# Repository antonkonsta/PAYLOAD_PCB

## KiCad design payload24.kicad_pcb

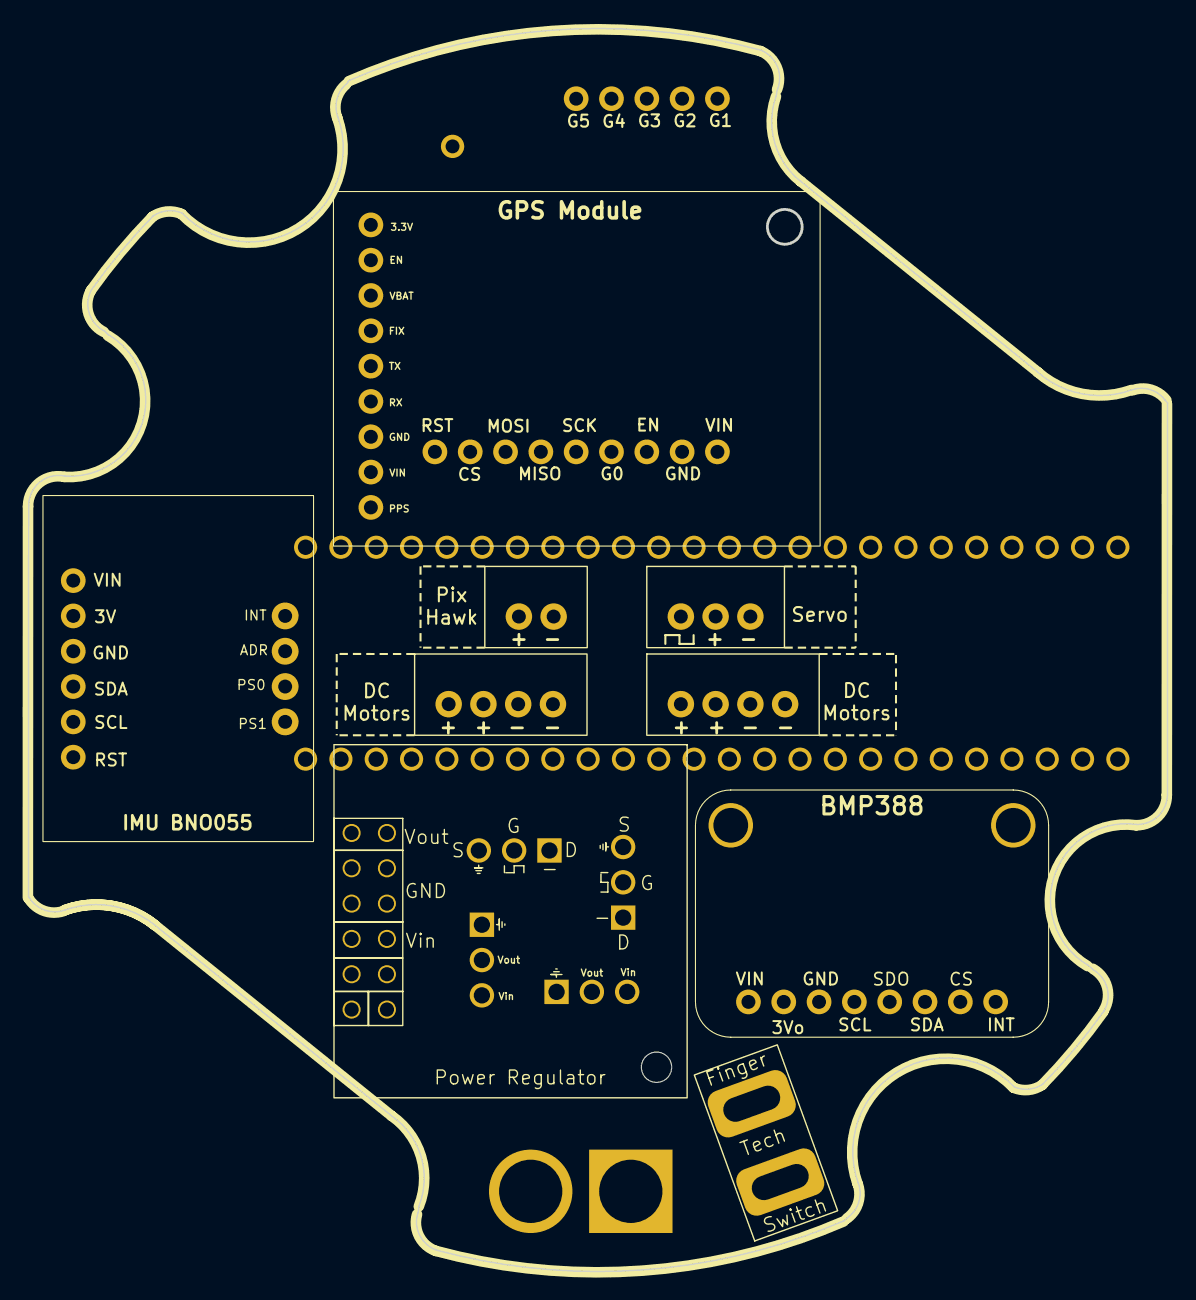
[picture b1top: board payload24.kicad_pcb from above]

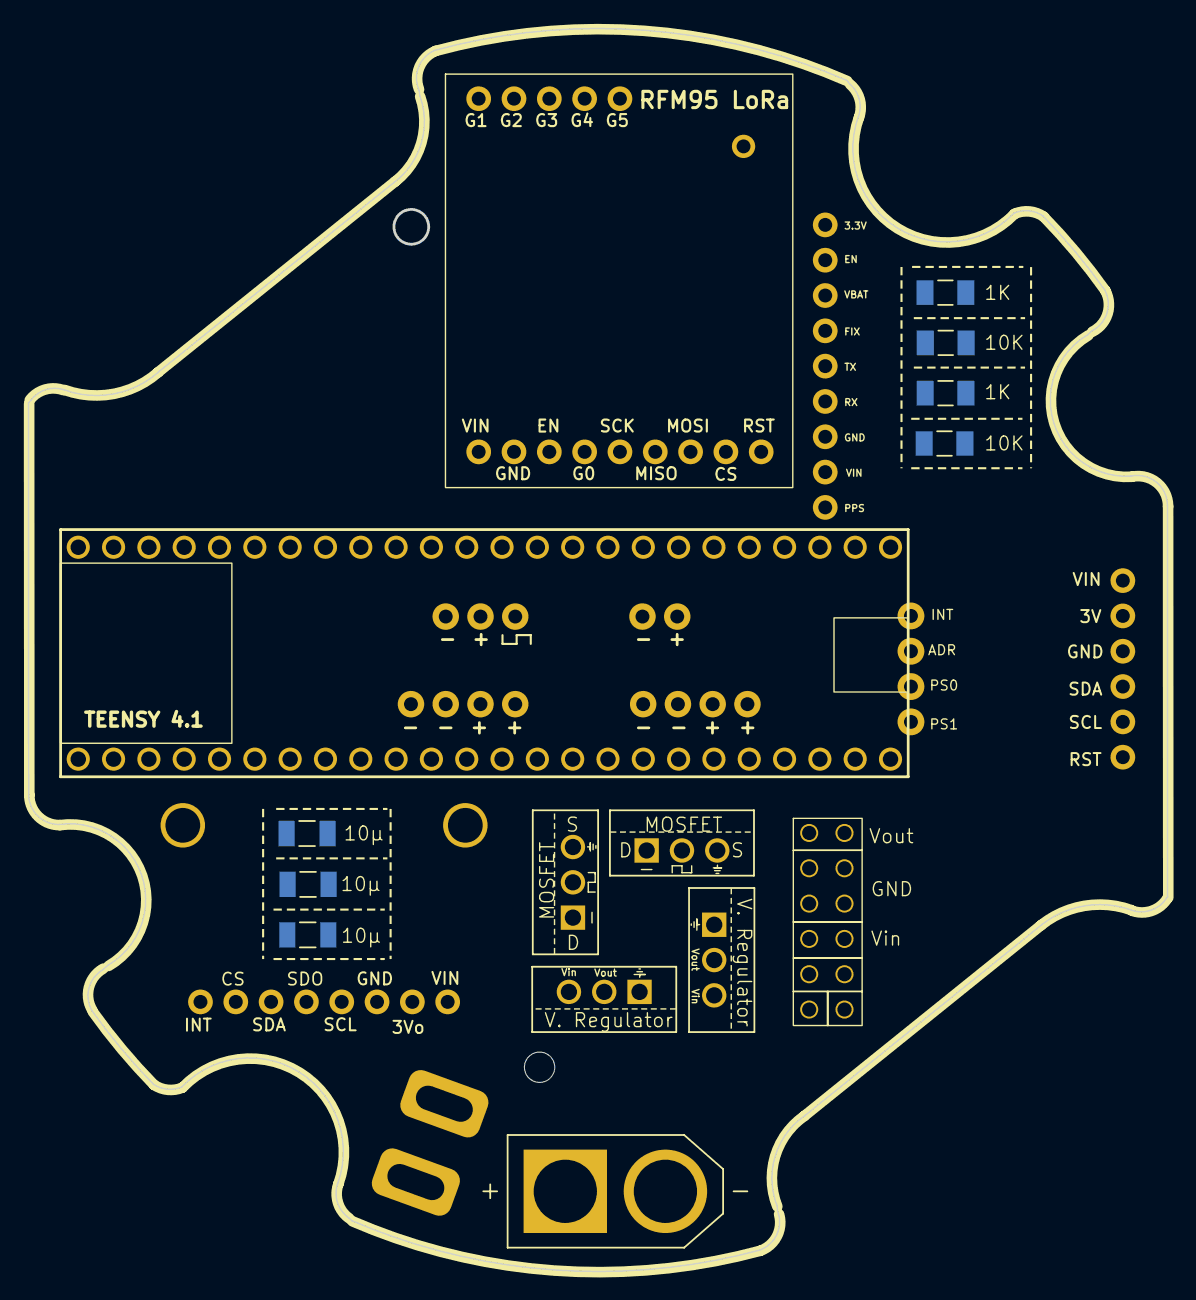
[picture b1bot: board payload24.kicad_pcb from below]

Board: 6 copper layers, 81.9 x 89.4 mm, 23 parts (14 on the bottom side), 28 nets, no tracks yet.

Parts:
C1, C2, C3: 10μF; CAPC3216X110N
J1: JST-XH3
J2: PixHawk; JST-XH2
J3, J4: Motors; JST-XH4
Q2: CSD19503KCS; teensyMosfet
Q3: IRLB4132; teensyMosfet
R2, R5: 1000; RESC3216X70N
R3, R6: 10K; RESC3216X70N
SW1: FingerTech
U1: TEENSY41
U2, U7: LMS1585ACT-3.3/NOPB; vRegulator
U3: GPS_adafruit
U4: RFM_LoRa
U5: VoltageRegulator
U6: AMASS_XT60-M
U8: BMP388
U14: BNO055

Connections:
3.3V-Teensy: U1.3.3V1 (3.3V), U8.1 (Vin), U14.1 (Vin)
3.3V-Teensy1: U1.3.3V2 (3.3V(250mA_max)), U3.2 (VIN)
5V-Power Reg.: C3.1, J1.2 (+), J2.1 (+), U1.Vin (Vin(3.6to5.5volts)), U2.3 (VI), U4.1 (VIN), U5.6 (VOUT), U7.3 (VI)
/22.2V: SW1.1 (A), U6.P (+)
/.1in: SW1.2 (B), U5.4 (VIN)
/Retention Signal: J1.1 (PWM), U1.23 (A9|CRX1|MCLK1|PWM)
CS: U1.36 (CS|PWM), U4.8 (CS)
EN1: U1.31 (CTX3), U3.8 (EN)
EN2: U1.10 (PWM|MQSR|CS), U4.3 (EN)
G0: U1.30 (CRX3), U4.4 (G0)
GND: C1.2, C2.2, C3.2, J1.3 (-), R3.1, R6.2, U1.GND1 (GND), U1.GND2 (GND), U1.GND3 (GND), U2.1 (GND), U3.3 (GND), U4.2 (GND), U5.5 (GND), U6.N (-), U7.1 (GND), U8.3 (GND), U14.3 (GND)
MISO: U1.12 (PWM|MQSL|MISO), U4.6 (MISO)
MOSI: U1.11 (PWM|CTX1|MOSI), U4.7 (MOSI)
unnamed: R2.2, R3.2
unnamed: J3.3 (-), J3.4 (-), J4.3 (-), J4.4 (-)
unnamed: R5.2, R6.1
unnamed: C1.1, J3.1 (+), J3.2 (+), U2.2 (VO)
unnamed: C2.1, J4.1 (+), J4.2 (+), U7.2 (VO)
Open Signal: R5.1, U1.27 (SCK1|A13)
RST2: U1.41 (A17), U14.6 (RST)
RST3: U1.2 (PWM|OUT2), U4.9 (RST)
RX1: U1.0 (PWM|CRX2|CS1|RX1), U3.4 (RX)
SCK: U1.13 ((LED)SCK), U4.5 (SCK)
SCL1: U1.16 (A2|RX4|SCL1), U8.4 (SCL)
SCL2: U1.24 (PWM|SCL2|TX6|A10), U14.4 (SCL)
SDA1: U1.17 (A3|TX4|SDA1), U8.6 (SDA)
SDA2: U1.25 (PWM|SDA2|RX6|A11), U14.5 (SDA)
TX1: U1.1 (PWM|CTX2|MISO1|TX1), U3.5 (TX)

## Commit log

2024-01-08 drill holes added
    Added drill holes for fastening PCB to payload
2024-01-08 PCB layer and power setup
    Made PCB 6-Layers
    Routed .1in power connection
    Setup power plane thermal relief spoke width and gap
    Moved Mosfet, power regular, and other components around a little
    Rotated PCB 21 degrees
2024-01-08 update (1/7/24)
2024-01-16 Update
    Updated .1in trace to be shorter
    removed one RF module pinhole and shifted BMP altimeter down
    Moved some traces and parts down
2024-01-16 updated pcb
    uploading unsaved changes
2024-01-29 final updates prior to purchasing (1/17)
2024-01-29 added arduino code folder
2024-02-11 PCB laid out
2024-02-13 Updates to PCB
2024-02-14 buzzermusic
2024-02-15 updated payload
2024-03-02 UPDATeEE
